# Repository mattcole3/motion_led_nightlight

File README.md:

motion_led_nightlight
=====================

code for an attiny85 nightlight

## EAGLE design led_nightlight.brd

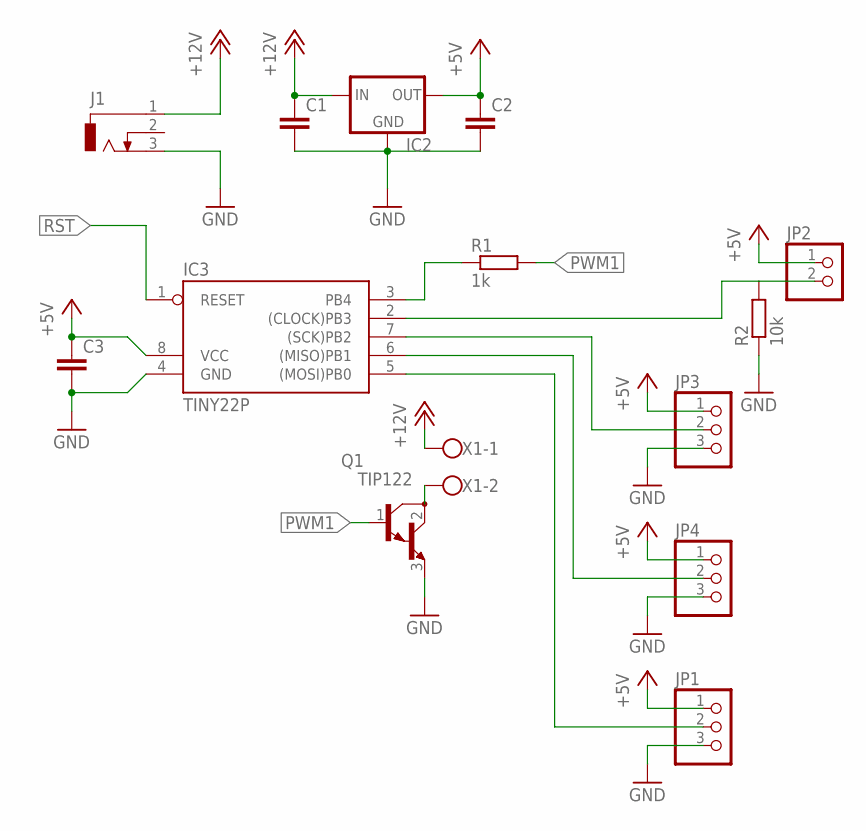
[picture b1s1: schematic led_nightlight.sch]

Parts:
C1, C2, C3: C-EU025-024X044; C025-024X044
IC2: 78XXL
IC3: TINY22P; DIL08
J1: DCJ0303
JP1, JP3, JP4: PINHD-1X3; 1X03
JP2: PINHD-1X2; 1X02
Q1: TIP122; TO220
R1: 1k; 0207/10
R2: 10k; 0207/10
X1: W237-102

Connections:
+5V: C2.1, C3.1, IC2.OUT, IC3.8 (VCC), JP1.1, JP2.1, JP3.1, JP4.1
+12V: C1.1, IC2.IN, J1.1, X1.1
GND: C1.2, C2.2, C3.2, IC2.GND, IC3.4 (GND), J1.3, JP1.3, JP3.3, JP4.3, Q1.3 (E), R2.1
MISO: IC3.6 ((MISO)PB1), JP4.2
MOSI: IC3.5 ((MOSI)PB0), JP1.2
unnamed: Q1.2 (C), X1.2
unnamed: IC3.3 (PB4), R1.1
unnamed: IC3.2 ((CLOCK)PB3), JP2.2, R2.2
PWM1: Q1.1 (B), R1.2
RST: IC3.1 (RESET)
SCK: IC3.7 ((SCK)PB2), JP3.2

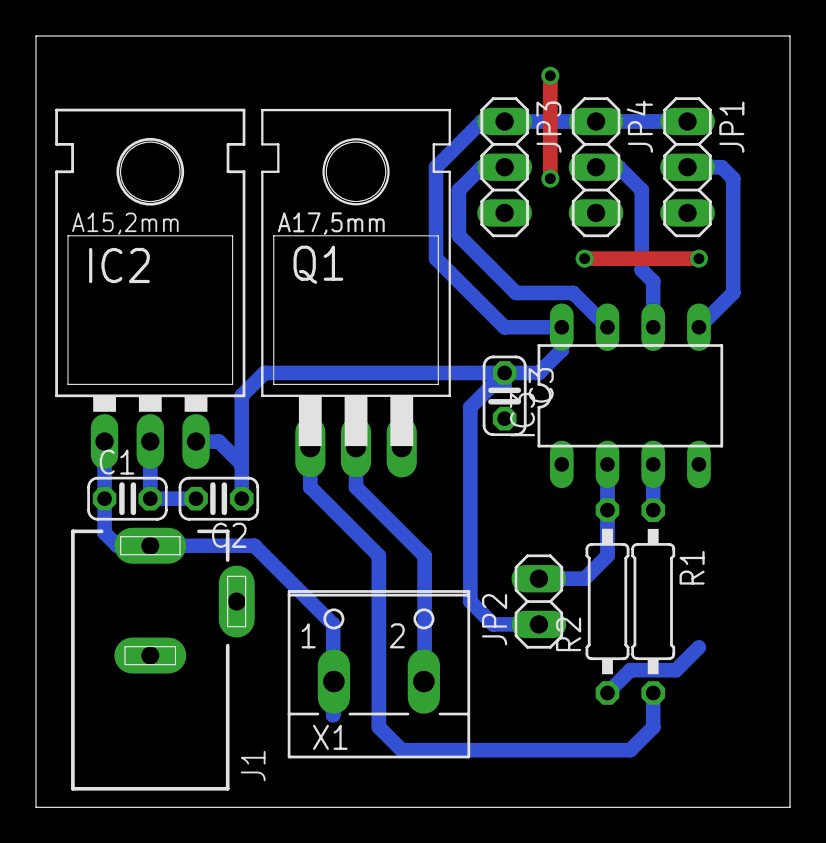
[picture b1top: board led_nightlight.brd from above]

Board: 2 copper layers, 41.9 x 42.9 mm, 14 parts (0 on the bottom side), 10 nets.

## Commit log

2014-10-04 initial drop of project files
